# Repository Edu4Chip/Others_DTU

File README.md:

# Others_DTU
This repository holds Edu4Chip-related projects and activities from DTU.

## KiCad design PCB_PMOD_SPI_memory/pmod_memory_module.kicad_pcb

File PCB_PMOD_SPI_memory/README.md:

# PMOD SPI Memory PCB Board

This is a PMOD module which has space for two SPI memories. Supported footprints are:
* SOIC-8 150 mil and SOIC-8 200 mil (combined in one footprint)
* TSSOP-8 

SOIC-8 footprints are on the topside and TSSOP-8 are on the backside. 

**IMPORTANT:** For one footprint either the SOIC-8 footprint can be used or TSSO-8 both *cannot* be used at once. 

1st SPI memory can either be soldered on U0 or U1 (U0 and U1 cannot both be used at once)

2nd SPI memory can either be soldered on U2 or U3 (U2 and U3 cannot both be used at once)

## PMOD Pinout
The PMOD connector pinout follows the [specification from Digilent](https://digilent.com/reference/pmod/start)

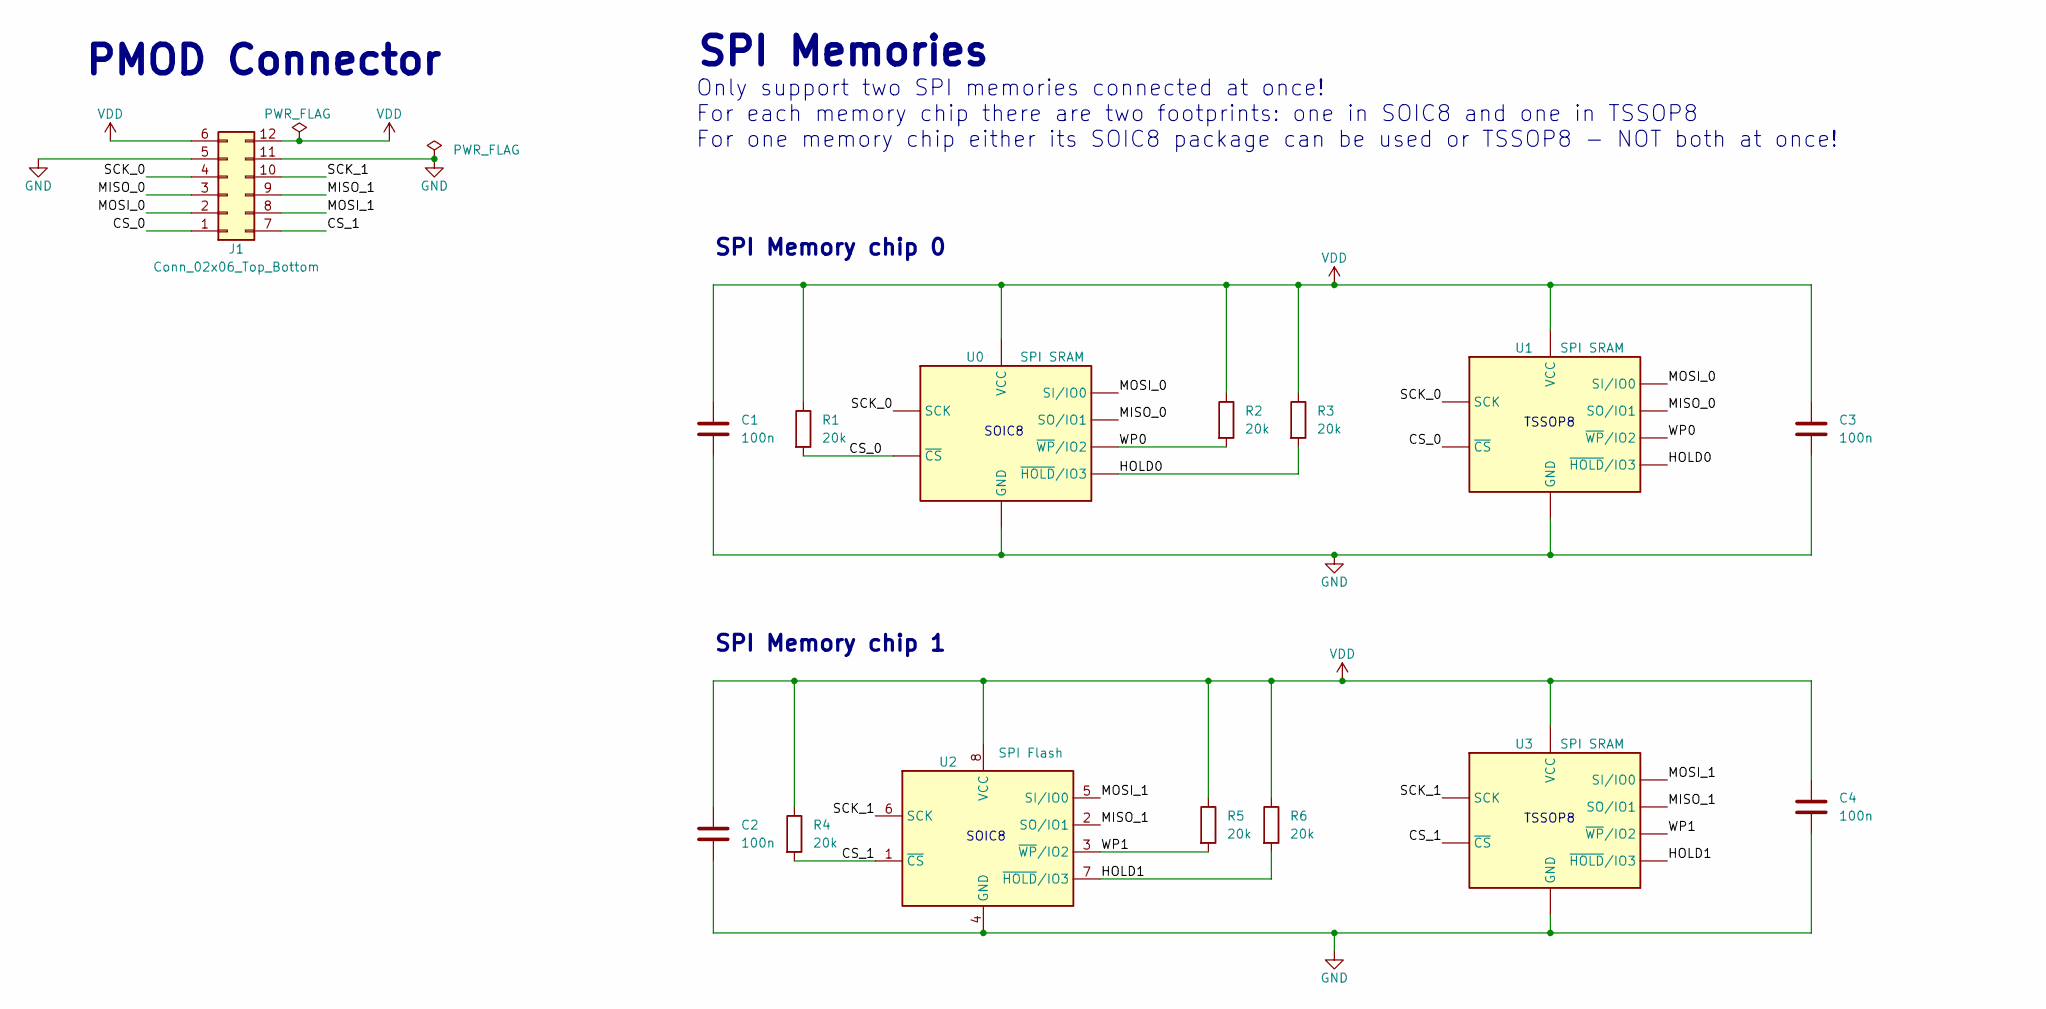
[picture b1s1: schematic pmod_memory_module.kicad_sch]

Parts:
C1, C2, C3, C4: 100n; C_0805_2012Metric_Pad1.18x1.45mm_HandSolder
J1: Conn_02x06_Top_Bottom; PinHeader_2x06_P2.54mm_Horizontal
R1, R2, R3, R4, R5, R6: 20k; R_0805_2012Metric_Pad1.20x1.40mm_HandSolder
U0: SPI SRAM; SOIC8_multi_150mil_and_200mil
U1, U3: SPI SRAM; TSSOP-8_4.4x3mm_P0.65mm
U2: SPI Flash; SOIC8_multi_150mil_and_200mil

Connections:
/CS_0: J1.1, R1.2, U0.1 (~CS), U1.1 (~CS)
/CS_1: J1.7, R4.2, U2.1 (~CS), U3.1 (~CS)
/HOLD0: R3.2, U0.7 (~HOLD/IO3), U1.7 (~HOLD/IO3)
/HOLD1: R6.2, U2.7 (~HOLD/IO3), U3.7 (~HOLD/IO3)
/MISO_0: J1.3, U0.2 (SO/IO1), U1.2 (SO/IO1)
/MISO_1: J1.9, U2.2 (SO/IO1), U3.2 (SO/IO1)
/MOSI_0: J1.2, U0.5 (SI/IO0), U1.5 (SI/IO0)
/MOSI_1: J1.8, U2.5 (SI/IO0), U3.5 (SI/IO0)
/SCK_0: J1.4, U0.6 (SCK), U1.6 (SCK)
/SCK_1: J1.10, U2.6 (SCK), U3.6 (SCK)
/WP0: R2.2, U0.3 (~WP/IO2), U1.3 (~WP/IO2)
/WP1: R5.2, U2.3 (~WP/IO2), U3.3 (~WP/IO2)
GND: C1.2, C2.2, C3.2, C4.2, J1.5, J1.11, U0.4 (GND), U1.4 (GND), U2.4 (GND), U3.4 (GND)
VDD: C1.1, C2.1, C3.1, C4.1, J1.6, J1.12, R1.1, R2.1, R3.1, R4.1, R5.1, R6.1, U0.8 (VCC), U1.8 (VCC), U2.8 (VCC), U3.8 (VCC)

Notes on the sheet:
SPI Memories
SOIC8
SPI Memory chip 1
TSSOP8
Only support two SPI memories connected at once! For each memory chip there are two footprints: one in SOIC8 and one in TSSOP8 For one memory chip either its SOIC8 package can be used or TSSOP8 - NOT both at once!
PMOD Connector
SPI Memory chip 0

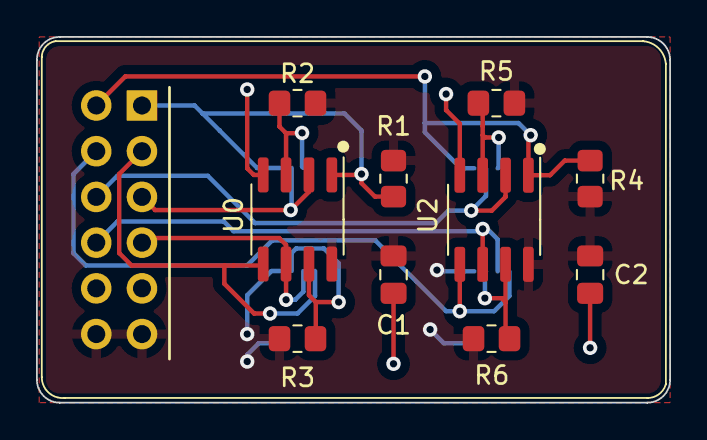
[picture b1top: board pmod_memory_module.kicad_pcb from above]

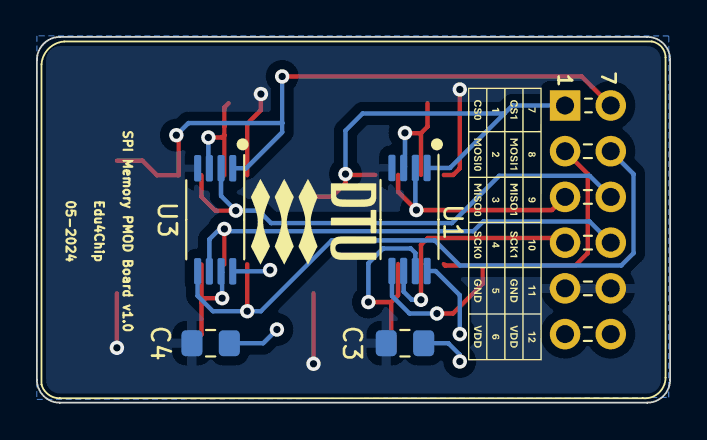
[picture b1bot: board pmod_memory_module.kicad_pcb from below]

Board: 2 copper layers, 35.2 x 20.3 mm, 15 parts (5 on the bottom side), 14 nets.

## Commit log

2024-05-27 PMOD SPI memory PCB
2024-05-27 Update PMOD pinout image
2024-06-17 constraint file for connecting pmod spi memory module to basys3 board
